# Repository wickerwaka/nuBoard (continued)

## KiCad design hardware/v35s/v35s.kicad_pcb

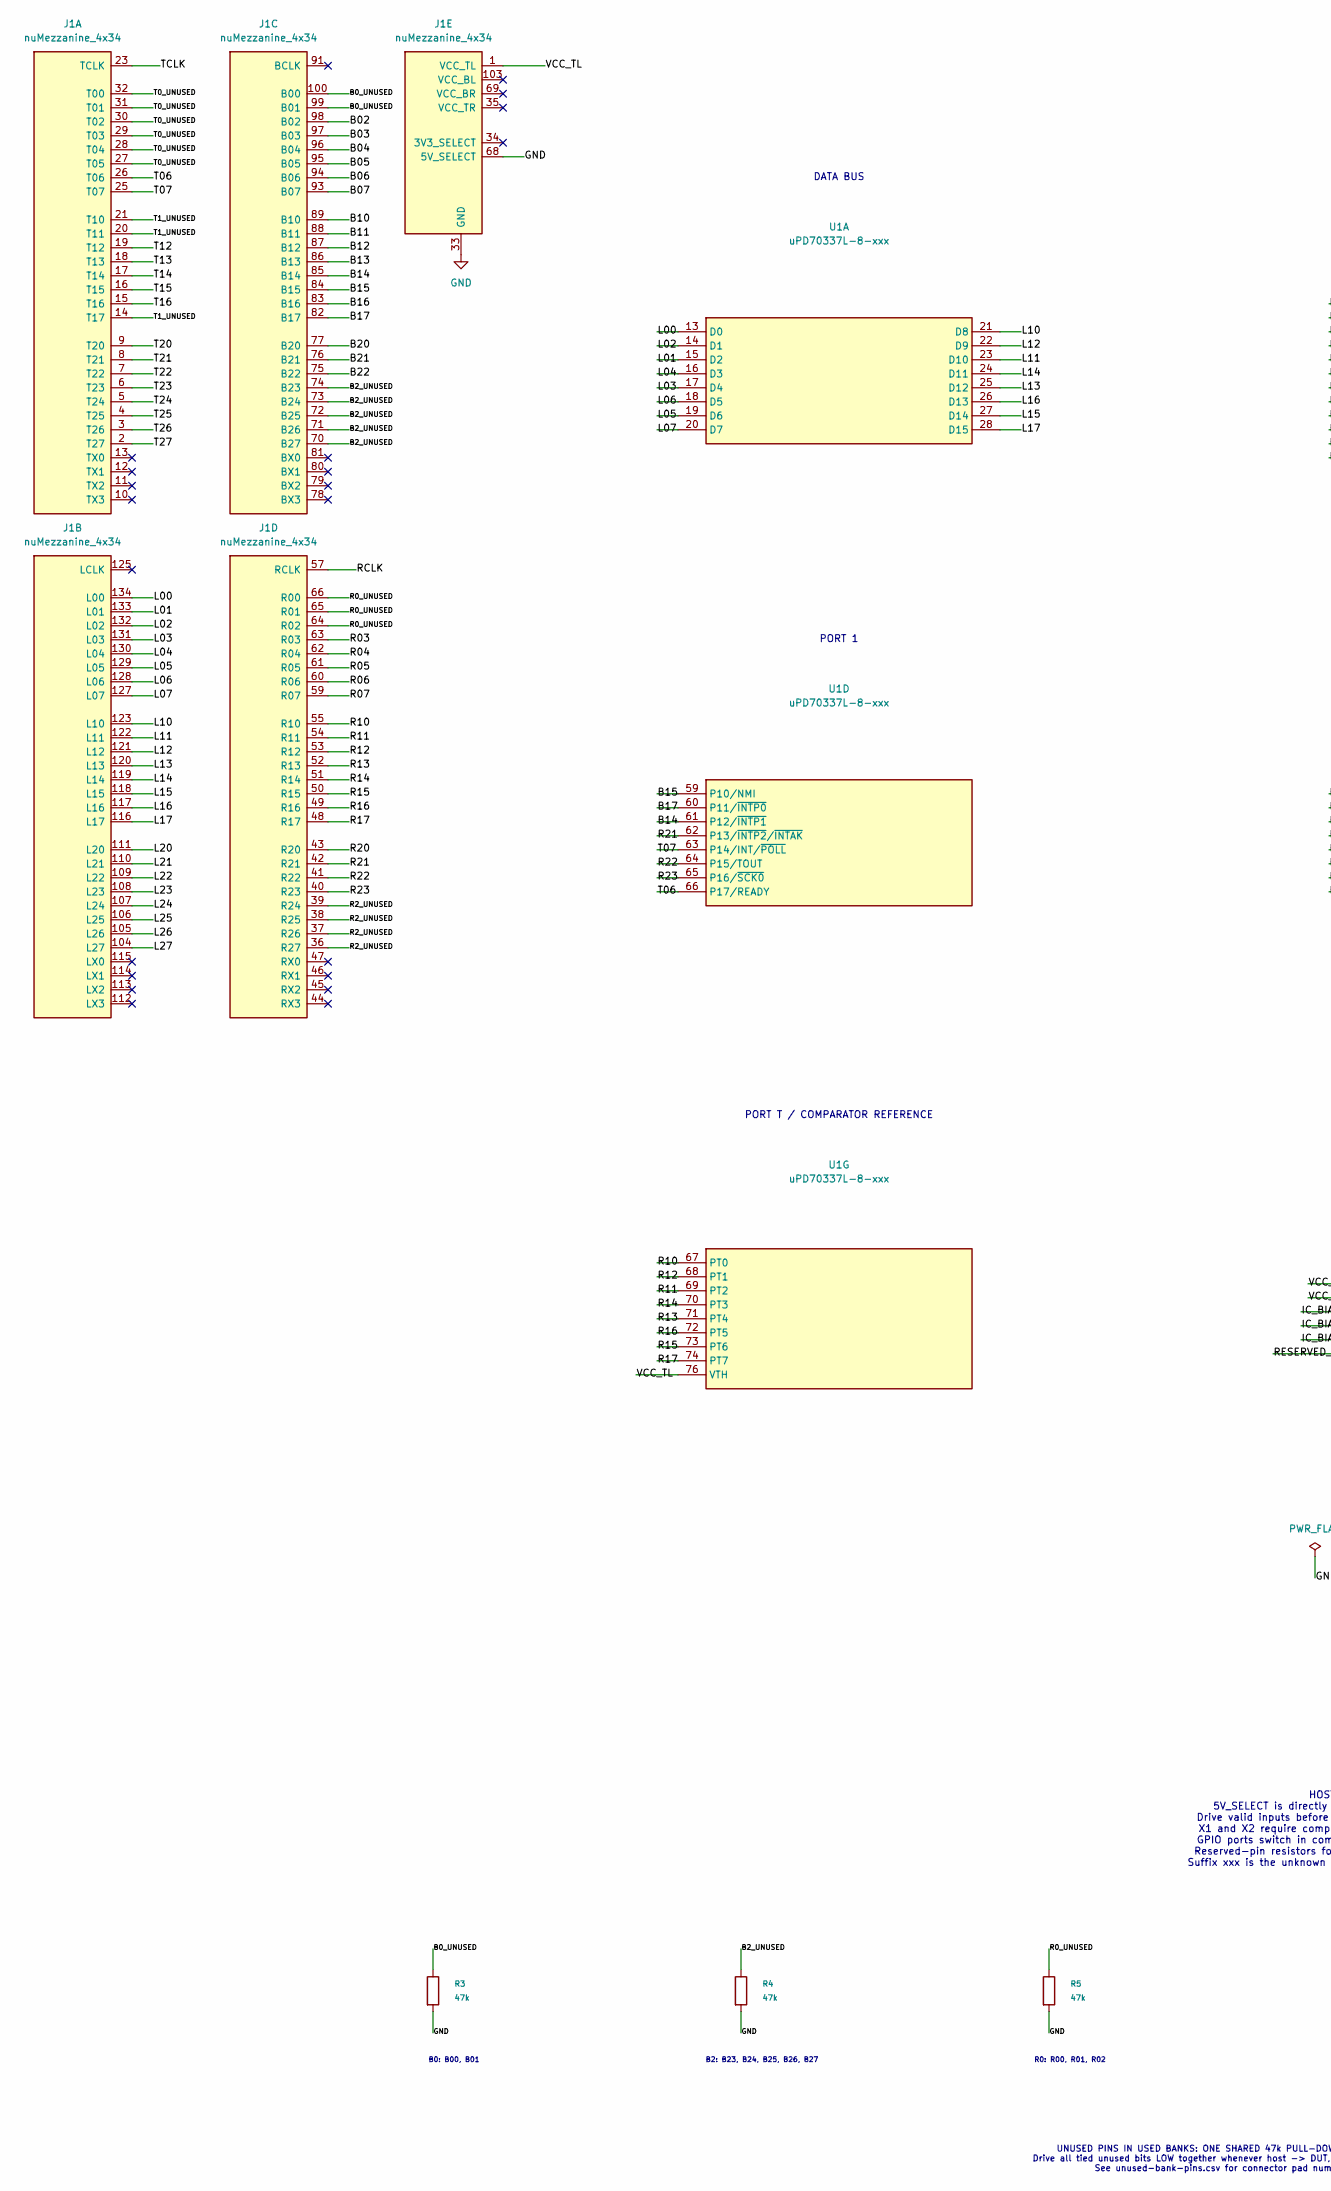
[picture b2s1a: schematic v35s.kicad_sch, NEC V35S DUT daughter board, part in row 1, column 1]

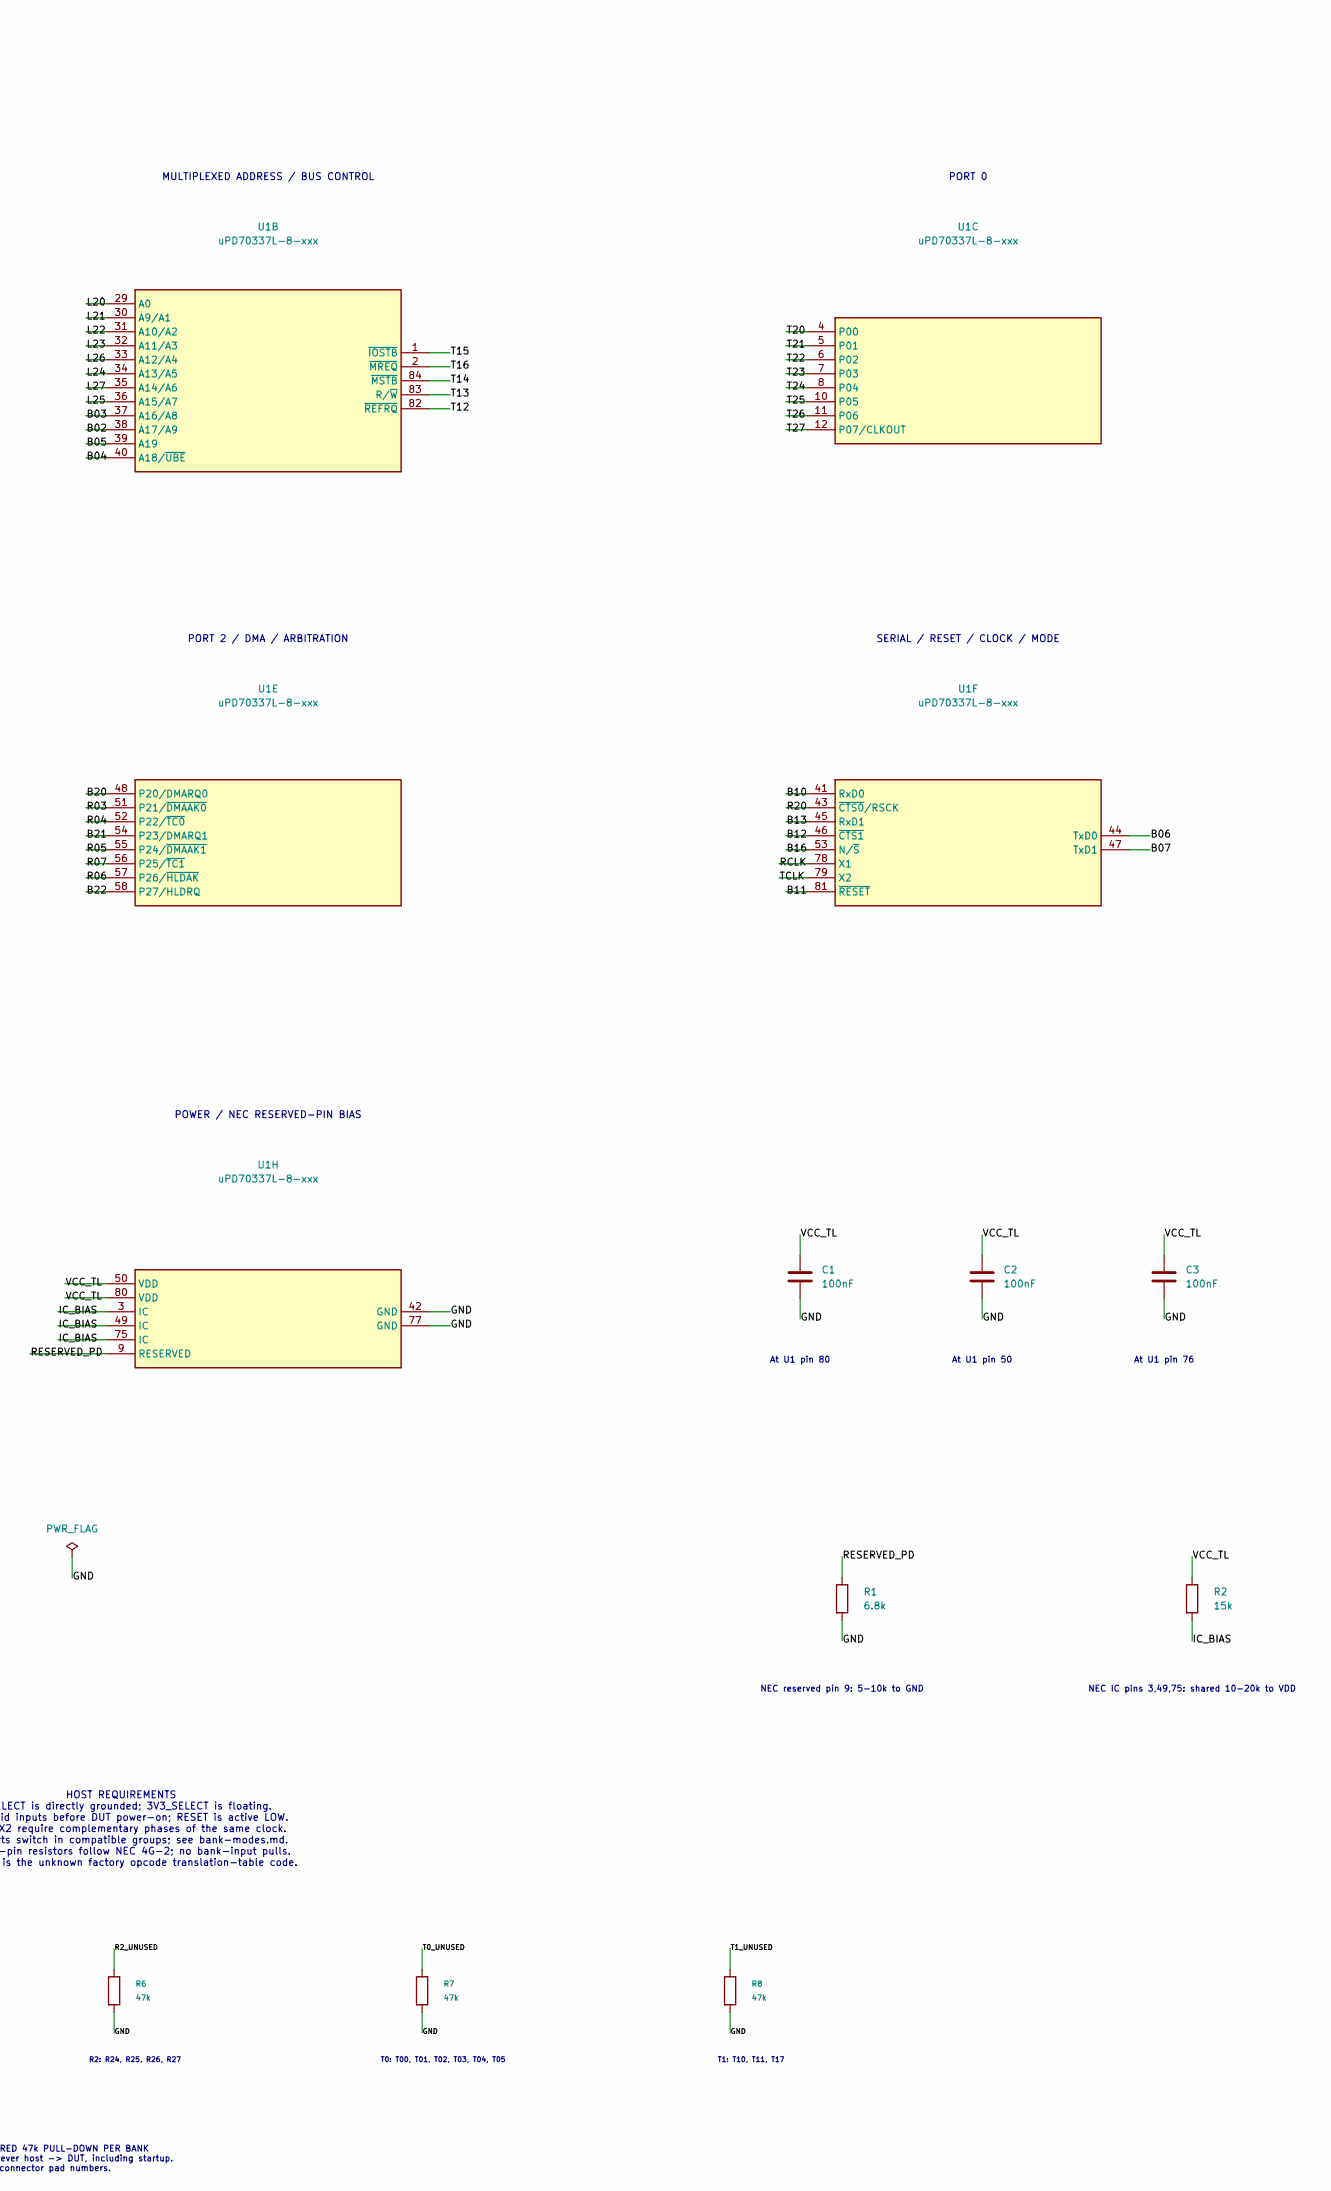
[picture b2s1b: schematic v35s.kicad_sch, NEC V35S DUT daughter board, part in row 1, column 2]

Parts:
C1, C2, C3: 100nF; C_0805_2012Metric_Pad1.18x1.45mm_HandSolder; Voltage 50V
J1: nuMezzanine_4x34; nuMezzanine_4x34_P2.54mm
R1: 6.8k; R_0805_2012Metric_Pad1.20x1.40mm_HandSolder
R2: 15k; R_0805_2012Metric_Pad1.20x1.40mm_HandSolder
R3, R4, R5, R6, R7, R8: 47k; R_0805_2012Metric_Pad1.20x1.40mm_HandSolder
U1: uPD70337L-8-xxx; PLCC-84_THT-Socket

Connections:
/B0_UNUSED: J1.99 (B01_99), J1.100 (B00_100), R3.1
/B02: J1.98 (B02_98), U1.38 (A17/A9)
/B2_UNUSED: J1.70 (B27_70), J1.71 (B26_71), J1.72 (B25_72), J1.73 (B24_73), J1.74 (B23_74), R4.1
/B03: J1.97 (B03_97), U1.37 (A16/A8)
/B04: J1.96 (B04_96), U1.40 (A18/~UBE)
/B05: J1.95 (B05_95), U1.39 (A19)
/B06: J1.94 (B06_94), U1.44 (TxD0)
/B07: J1.93 (B07_93), U1.47 (TxD1)
/B10: J1.89 (B10_89), U1.41 (RxD0)
/B11: J1.88 (B11_88), U1.81 (~RESET)
/B12: J1.87 (B12_87), U1.46 (~CTS1)
/B13: J1.86 (B13_86), U1.45 (RxD1)
/B14: J1.85 (B14_85), U1.61 (P12/~INTP1)
/B15: J1.84 (B15_84), U1.59 (P10/NMI)
/B16: J1.83 (B16_83), U1.53 (N/~S)
/B17: J1.82 (B17_82), U1.60 (P11/~INTP0)
/B20: J1.77 (B20_77), U1.48 (P20/DMARQ0)
/B21: J1.76 (B21_76), U1.54 (P23/DMARQ1)
/B22: J1.75 (B22_75), U1.58 (P27/HLDRQ)
/IC_BIAS: R2.2, U1.3 (IC), U1.49 (IC), U1.75 (IC)
/L00: J1.134 (L00_134), U1.13 (D0)
/L01: J1.133 (L01_133), U1.15 (D2)
/L02: J1.132 (L02_132), U1.14 (D1)
/L03: J1.131 (L03_131), U1.17 (D4)
/L04: J1.130 (L04_130), U1.16 (D3)
/L05: J1.129 (L05_129), U1.19 (D6)
/L06: J1.128 (L06_128), U1.18 (D5)
/L07: J1.127 (L07_127), U1.20 (D7)
/L10: J1.123 (L10_123), U1.21 (D8)
/L11: J1.122 (L11_122), U1.23 (D10)
/L12: J1.121 (L12_121), U1.22 (D9)
/L13: J1.120 (L13_120), U1.25 (D12)
/L14: J1.119 (L14_119), U1.24 (D11)
/L15: J1.118 (L15_118), U1.27 (D14)
/L16: J1.117 (L16_117), U1.26 (D13)
/L17: J1.116 (L17_116), U1.28 (D15)
/L20: J1.111 (L20_111), U1.29 (A0)
/L21: J1.110 (L21_110), U1.30 (A9/A1)
/L22: J1.109 (L22_109), U1.31 (A10/A2)
/L23: J1.108 (L23_108), U1.32 (A11/A3)
/L24: J1.107 (L24_107), U1.34 (A13/A5)
/L25: J1.106 (L25_106), U1.36 (A15/A7)
/L26: J1.105 (L26_105), U1.33 (A12/A4)
/L27: J1.104 (L27_104), U1.35 (A14/A6)
/R0_UNUSED: J1.64 (R02_64), J1.65 (R01_65), J1.66 (R00_66), R5.1
/R2_UNUSED: J1.36 (R27_36), J1.37 (R26_37), J1.38 (R25_38), J1.39 (R24_39), R6.1
/R03: J1.63 (R03_63), U1.51 (P21/~DMAAK0)
/R04: J1.62 (R04_62), U1.52 (P22/~TC0)
/R05: J1.61 (R05_61), U1.55 (P24/~DMAAK1)
/R06: J1.60 (R06_60), U1.57 (P26/~HLDAK)
/R07: J1.59 (R07_59), U1.56 (P25/~TC1)
/R10: J1.55 (R10_55), U1.67 (PT0)
/R11: J1.54 (R11_54), U1.69 (PT2)
/R12: J1.53 (R12_53), U1.68 (PT1)
/R13: J1.52 (R13_52), U1.71 (PT4)
/R14: J1.51 (R14_51), U1.70 (PT3)
/R15: J1.50 (R15_50), U1.73 (PT6)
/R16: J1.49 (R16_49), U1.72 (PT5)
/R17: J1.48 (R17_48), U1.74 (PT7)
/R20: J1.43 (R20_43), U1.43 (~CTS0/RSCK)
/R21: J1.42 (R21_42), U1.62 (P13/~INTP2/~INTAK)
/R22: J1.41 (R22_41), U1.64 (P15/TOUT)
/R23: J1.40 (R23_40), U1.65 (P16/~SCK0)
/RCLK: J1.57 (RCLK_57), U1.78 (X1)
/RESERVED_PD: R1.1, U1.9 (RESERVED)
/T0_UNUSED: J1.27 (T05_27), J1.28 (T04_28), J1.29 (T03_29), J1.30 (T02_30), J1.31 (T01_31), J1.32 (T00_32), R7.1
/T1_UNUSED: J1.14 (T17_14), J1.20 (T11_20), J1.21 (T10_21), R8.1
/T06: J1.26 (T06_26), U1.66 (P17/READY)
/T07: J1.25 (T07_25), U1.63 (P14/INT/~POLL)
/T12: J1.19 (T12_19), U1.82 (~REFRQ)
/T13: J1.18 (T13_18), U1.83 (R/~W)
/T14: J1.17 (T14_17), U1.84 (~MSTB)
/T15: J1.16 (T15_16), U1.1 (~IOSTB)
/T16: J1.15 (T16_15), U1.2 (~MREQ)
/T20: J1.9 (T20_9), U1.4 (P00)
/T21: J1.8 (T21_8), U1.5 (P01)
/T22: J1.7 (T22_7), U1.6 (P02)
/T23: J1.6 (T23_6), U1.7 (P03)
/T24: J1.5 (T24_5), U1.8 (P04)
/T25: J1.4 (T25_4), U1.10 (P05)
/T26: J1.3 (T26_3), U1.11 (P06)
/T27: J1.2 (T27_2), U1.12 (P07/CLKOUT)
/TCLK: J1.23 (TCLK_23), U1.79 (X2)
/VCC_TL: C1.1, C2.1, C3.1, J1.1 (VCC_TL_1), R2.1, U1.50 (VDD), U1.76 (VTH), U1.80 (VDD)
GND: C1.2, C2.2, C3.2, J1.22 (GND_22), J1.24 (GND_24), J1.33 (GND_33), J1.56 (GND_56), J1.58 (GND_58), J1.67 (GND_67), J1.68 (5V_SELECT_68), J1.90 (GND_90), J1.92 (GND_92), J1.101 (GND_101), J1.102 (GND), J1.124 (GND_124), J1.126 (GND_126), J1.135 (GND_135), J1.136 (GND), R1.2, R3.2, R4.2, R5.2, R6.2, R7.2, R8.2, U1.42 (GND), U1.77 (GND)

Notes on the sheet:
DATA BUS
MULTIPLEXED ADDRESS / BUS CONTROL
PORT 0
PORT 1
PORT 2 / DMA / ARBITRATION
SERIAL / RESET / CLOCK / MODE
PORT T / COMPARATOR REFERENCE
POWER / NEC RESERVED-PIN BIAS
At U1 pin 80
At U1 pin 50
At U1 pin 76
NEC reserved pin 9: 5-10k to GND
NEC IC pins 3,49,75: shared 10-20k to VDD
HOST REQUIREMENTS 5V_SELECT is directly grounded; 3V3_SELECT is floating. Drive valid inputs before DUT power-on; RESET is active LOW. X1 and X2 require complementary phases of the same clock. GPIO ports switch in compatible groups; see bank-modes.md. Reserved-pin resistors follow NEC 4G-2; no bank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
B0: B00, B01
B2: B23, B24, B25, B26, B27
R0: R00, R01, R02
R2: R24, R25, R26, R27
T0: T00, T01, T02, T03, T04, T05
T1: T10, T11, T17
UNUSED PINS IN USED BANKS: ONE SHARED 47k PULL-DOWN PER BANK Drive all tied unused bits LOW together whenever host -> DUT, including startup. See unused-bank-pins.csv for connector pad numbers.

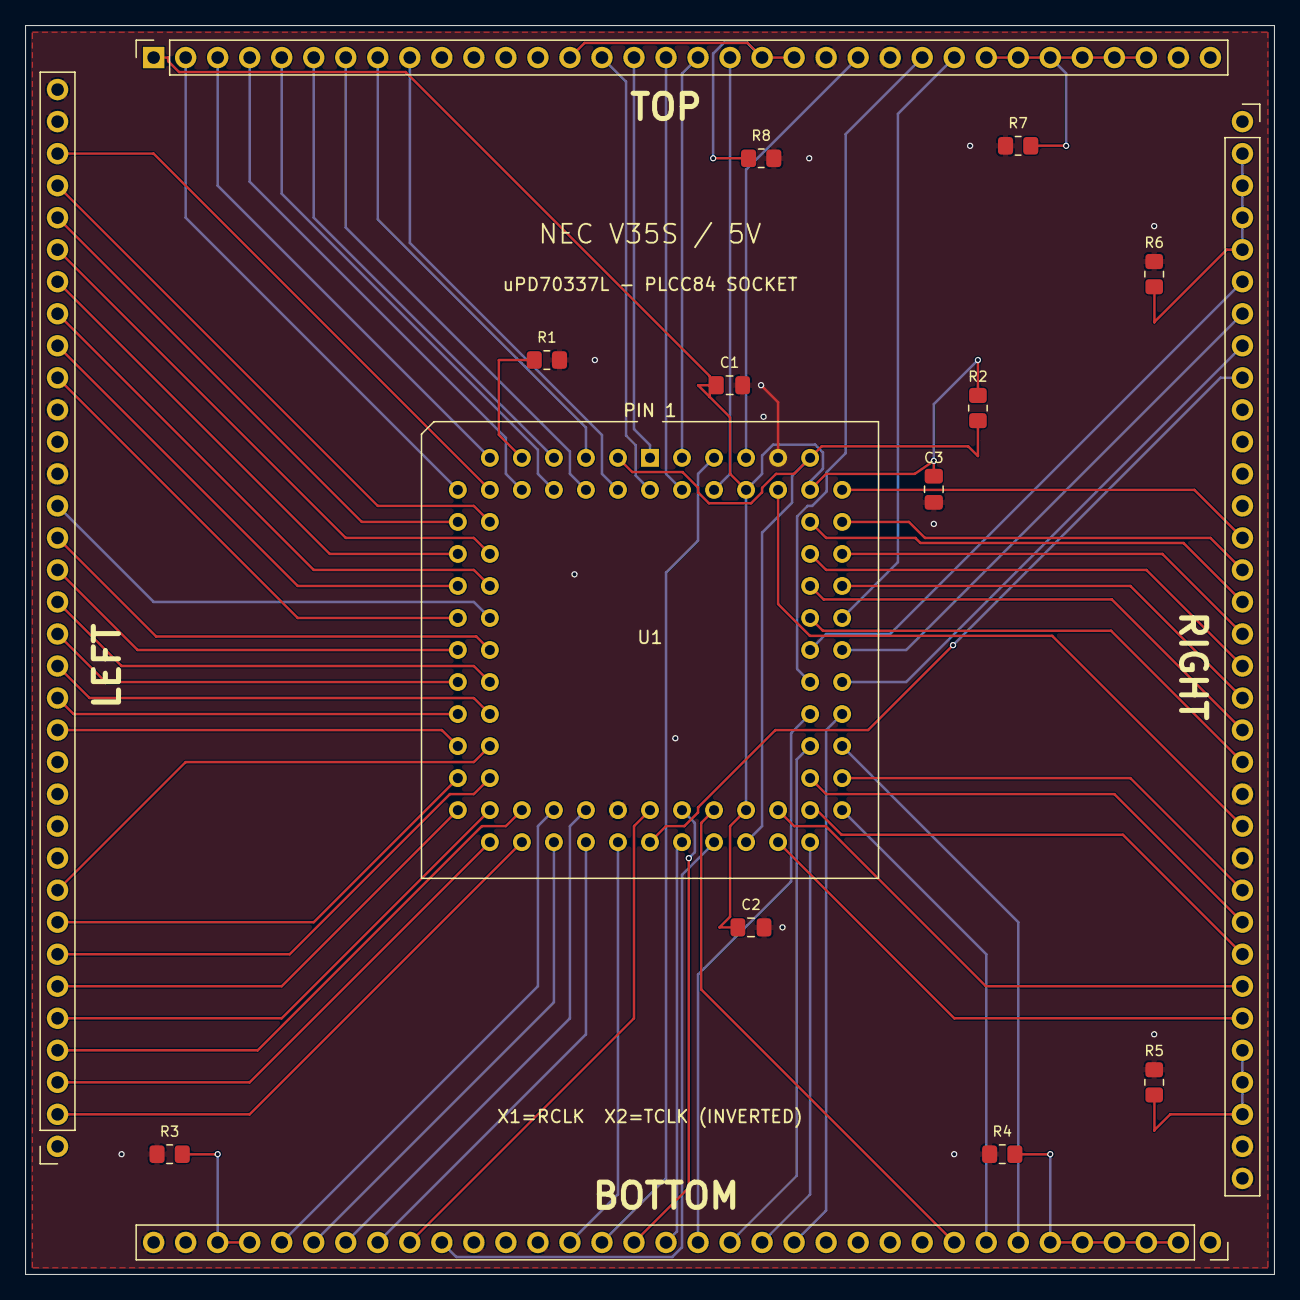
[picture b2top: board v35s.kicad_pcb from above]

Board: 2 copper layers, 99.1 x 99.1 mm, 13 parts (0 on the bottom side), 85 nets.

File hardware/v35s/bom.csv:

Reference,Quantity,Value/part,Package,Notes
U1,1,NEC uPD70337L-8-xxx,84-pin PLCC,Factory opcode-table suffix unknown; user-selected package
U1 socket,1,Assmann A-CCS 084-Z-T,84-pin through-hole PLCC socket,ASS0981CO rev11; 2.54mm grid; 0.8mm holes
C1 C2 C3,3,100nF ceramic >=50V,0805 SMD HandSolder,Prefer X7R; enlarged hand-solder pads
R1,1,6.8k 1% >=0.25W,0805 SMD HandSolder,NEC required reserved-pin pull-down
R2,1,15k 1% >=0.25W,0805 SMD HandSolder,NEC required shared IC-pin pull-up
J1,1,nuBoard mezzanine mating contact set,Four 34-position rows 2.54mm pitch,Use mating connector height and gender matching the existing host; template geometry retained
R3,1,47k 1% >=0.25W,0805 SMD HandSolder,B0 shared unused-bit pull-down to GND
R4,1,47k 1% >=0.25W,0805 SMD HandSolder,B2 shared unused-bit pull-down to GND
R5,1,47k 1% >=0.25W,0805 SMD HandSolder,R0 shared unused-bit pull-down to GND
R6,1,47k 1% >=0.25W,0805 SMD HandSolder,R2 shared unused-bit pull-down to GND
R7,1,47k 1% >=0.25W,0805 SMD HandSolder,T0 shared unused-bit pull-down to GND
R8,1,47k 1% >=0.25W,0805 SMD HandSolder,T1 shared unused-bit pull-down to GND
